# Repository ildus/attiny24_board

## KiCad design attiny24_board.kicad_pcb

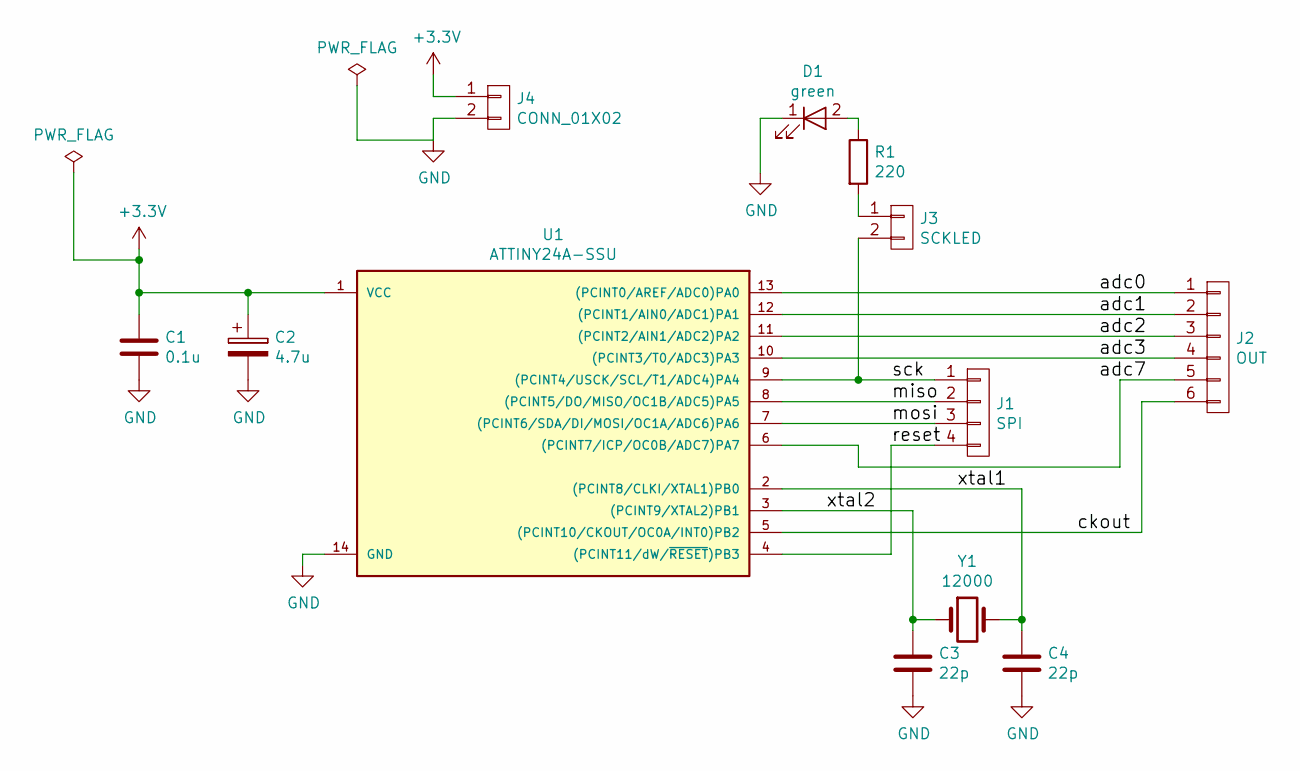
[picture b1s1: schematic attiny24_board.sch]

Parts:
C1: 0.1u; C_0805
C2: 4.7u; CP_Elec_4x4.5
C3, C4: 22p; C_0805
D1: green; LED_1206
J1: SPI; Molex_KK-6410-04_04x2.54mm_Straight
J2: OUT; Molex_KK-6410-06_06x2.54mm_Straight
J3: SCKLED; Molex_KK-6410-02_02x2.54mm_Straight
J4: CONN_01X02; Molex_KK-6410-02_02x2.54mm_Straight
R1: 220
U1: ATTINY24A-SSU; SOIC-14_3.9x8.7mm_Pitch1.27mm
Y1: 12000; Crystal_HC50_Vertical

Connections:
+3V3: C1.1, C2.1, J4.1, U1.1 (VCC)
/adc0: J2.1, U1.13 ((PCINT0/AREF/ADC0)PA0)
/adc1: J2.2, U1.12 ((PCINT1/AIN0/ADC1)PA1)
/adc2: J2.3, U1.11 ((PCINT2/AIN1/ADC2)PA2)
/adc3: J2.4, U1.10 ((PCINT3/T0/ADC3)PA3)
/ckout: J2.6, U1.5 ((PCINT10/CKOUT/OC0A/INT0)PB2)
/miso: J1.2, U1.8 ((PCINT5/DO/MISO/OC1B/ADC5)PA5)
/mosi: J1.3, U1.7 ((PCINT6/SDA/DI/MOSI/OC1A/ADC6)PA6)
/reset: J1.4, U1.4 ((PCINT11/dW/~RESET~)PB3)
/sck: J1.1, J3.2, U1.9 ((PCINT4/USCK/SCL/T1/ADC4)PA4)
/xtal1: C4.1, U1.2 ((PCINT8/CLKI/XTAL1)PB0), Y1.2
/xtal2: C3.1, U1.3 ((PCINT9/XTAL2)PB1), Y1.1
GND: C1.2, C2.2, C3.2, C4.2, D1.1 (K), J4.2, U1.14 (GND)
unnamed: D1.2 (A), R1.1
unnamed: J2.5, U1.6 ((PCINT7/ICP/OC0B/ADC7)PA7)
unnamed: J3.1, R1.2

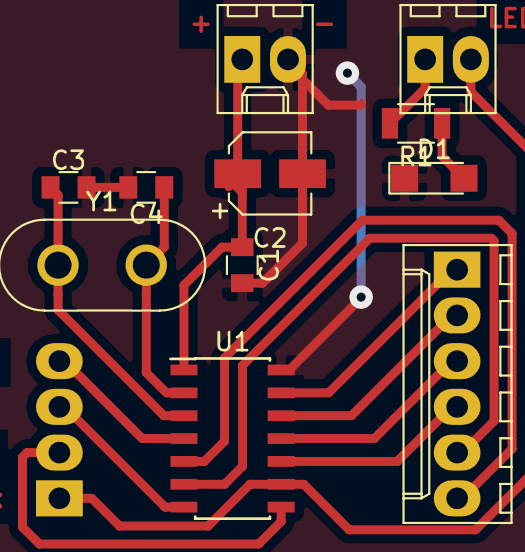
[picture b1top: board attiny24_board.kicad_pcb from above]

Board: 2 copper layers, 12 parts (1 on the bottom side), 16 nets.

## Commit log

2017-06-06 initial
2017-06-08 Make changes
2017-06-08 Add forgoteen resistor
